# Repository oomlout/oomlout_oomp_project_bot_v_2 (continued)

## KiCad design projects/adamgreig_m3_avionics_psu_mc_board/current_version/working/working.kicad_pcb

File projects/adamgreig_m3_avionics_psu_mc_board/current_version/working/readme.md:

# m3_avionics
 
## summary 
* id: adamgreig_m3_avionics_psu_mc_board
* user: adamgreig
* name: m3_avionics
* board: psu_mc_board
* repo: https://github.com/adamgreig/m3-avionics
* src_file_repo_kicad_pcb: m3psu/pcb/PSU-MC-Board/PSU-MC-Board.kicad_pcb
* src_file_repo_kicad_pcb_link: https://github.com/adamgreig/m3-avionics/tree/master/m3psu/pcb/PSU-MC-Board/PSU-MC-Board.kicad_pcb

* src_file_repo_sch: m3psu/pcb/PSU-MC-Board/PSU-MC-Board.sch
* src_file_repo_sch_link: https://github.com/adamgreig/m3-avionics/tree/master/m3psu/pcb/PSU-MC-Board/PSU-MC-Board.sch
* full details link: https://github.com/oomlout/oomlout_oomp_project_bot_v_2/tree/main/projects/adamgreig_m3_avionics_psu_mc_board/current_version/working  

## schematic  
  
[schematic (pdf)](working_schematic.pdf) 

## pcb  

[board (pdf)](working.pdf)  

## working_bom
| Id | Designator | Footprint | Quantity | Designation | Supplier and ref |  | None | 
| --- | --- | --- | --- | --- | --- | --- | --- | 
| 1 | C1,C2 | 0402 | 2 | 10p |  |  | [''] | 
| 2 | C3 | 0402 | 1 | 4Âµ7 |  |  | [''] | 
| 3 | C4,C5,C7,C8,C9,C16,C19,C20 | 0402 | 8 | 100n |  |  | [''] | 
| 4 | C6 | 0402 | 1 | 1Âµ |  |  | [''] | 
| 5 | C10,C11 | 0402 | 2 | 2Âµ2 |  |  | [''] | 
| 6 | C12,C14 | 0805 | 2 | 22Âµ |  |  | [''] | 
| 7 | C13 | 0402 | 1 | 3n3 |  |  | [''] | 
| 8 | IC1 | LQFP-64 | 1 | STM32F405RxTx |  |  | [''] | 
| 9 | IC2 | QFN-16-EP-TI | 1 | TPS62152 |  |  | [''] | 
| 10 | IC3 | DFN-8-EP-MICROCHIP | 1 | MCP2562 |  |  | [''] | 
| 11 | IC5 | DFN-10-EP-LT | 1 | LTC4151 |  |  | [''] | 
| 12 | J1 | TFML-110-02-L-D | 1 | WEST TOP |  |  | [''] | 
| 13 | J3 | TFML-105-02-L-D | 1 | NORTH TOP |  |  | [''] | 
| 14 | J4 | TFML-110-02-L-D | 1 | EAST TOP |  |  | [''] | 
| 15 | L1 | VLS201610HBX-1 | 1 | 3Âµ3 |  |  | [''] | 
| 16 | Q9,Q2 | SOT-883-B | 2 | NFET |  |  | [''] | 
| 17 | R3 | 0402 | 1 | 100 |  |  | [''] | 
| 18 | R7,R8,R10 | 0402 | 3 | 4k7 |  |  | [''] | 
| 19 | R15 | 0805 | 1 | 10m |  |  | [''] | 
| 20 | R16,R23,R4,R5 | 0402 | 4 | 33k |  |  | [''] | 
| 21 | Y1 | XTAL-20x16 | 1 | 26M |  |  | [''] | 
| 22 | Q8,Q1 | SON2x2 | 2 | PFET |  |  | [''] | 
| 23 | R1,R2 | 0402 | 2 | 100k |  |  | [''] | 
| 24 | J2 | SFML-110-02-L-D-LC | 1 | WEST BOT |  |  | [''] | 
| 25 | J5 | SFML-110-02-L-D-LC | 1 | EAST BOT |  |  | [''] | 
| 26 | G*** | cusf_logo_full | 1 | LOGO |  |  | [''] | 

## bom_schematic
| Ref | Qnty | Value | Cmp name | Footprint | Description | Vendor | DNP | 
| --- | --- | --- | --- | --- | --- | --- | --- | 
| C1, C2 | 2 | 10p | C | agg:0402 |  |  |  | 
| C3 | 1 | 4Âµ7 | C | agg:0402 |  |  |  | 
| C4, C5, C7, C8, C9, C16, C19, C20 | 8 | 100n | C | agg:0402 |  |  |  | 
| C6 | 1 | 1Âµ | C | agg:0402 |  |  |  | 
| C10, C11 | 2 | 2Âµ2 | C | agg:0402 |  |  |  | 
| C12, C14 | 2 | 22Âµ | C | agg:0805 |  |  |  | 
| C13 | 1 | 3n3 | C | agg:0402 |  |  |  | 
| IC1 | 1 | STM32F405RxTx | STM32F405RxTx | agg:LQFP-64 |  |  |  | 
| IC2 | 1 | TPS62152 | TPS62152 | agg:QFN-16-EP-TI |  |  |  | 
| IC3 | 1 | MCP2562 | MCP2562 | agg:DFN-8-EP-MICROCHIP |  |  |  | 
| IC5 | 1 | LTC4151 | LTC4151 | agg:DFN-10-EP-LT |  |  |  | 
| J1 | 1 | WEST TOP | CONN_02x10 | agg:TFML-110-02-L-D |  |  |  | 
| J2 | 1 | WEST BOT | CONN_02x10 | agg:SFML-110-02-L-D-LC |  |  |  | 
| J3 | 1 | NORTH TOP | CONN_02x05 | agg:TFML-105-02-L-D |  |  |  | 
| J4 | 1 | EAST TOP | CONN_02x10 | agg:TFML-110-02-L-D |  |  |  | 
| J5 | 1 | EAST BOT | CONN_02x10 | agg:SFML-110-02-L-D-LC |  |  |  | 
| L1 | 1 | 3Âµ3 | L | agg:VLS201610HBX-1 |  |  |  | 
| Q1, Q8 | 2 | PFET | PFET_GDS | agg:SON2x2 |  |  |  | 
| Q2, Q9 | 2 | NFET | NFET_GDS | agg:SOT-883-B |  |  |  | 
| R1, R2 | 2 | 100k | R | agg:0402 |  |  |  | 
| R3 | 1 | 100 | R | agg:0402 |  |  |  | 
| R4, R5, R16, R23 | 4 | 33k | R | agg:0402 |  |  |  | 
| R7, R8, R10 | 3 | 4k7 | R | agg:0402 |  |  |  | 
| R15 | 1 | 10m | R | agg:0805 |  |  |  | 
| Y1 | 1 | 26M | SMD_XTAL | agg:XTAL-20x16 |  |  |  |

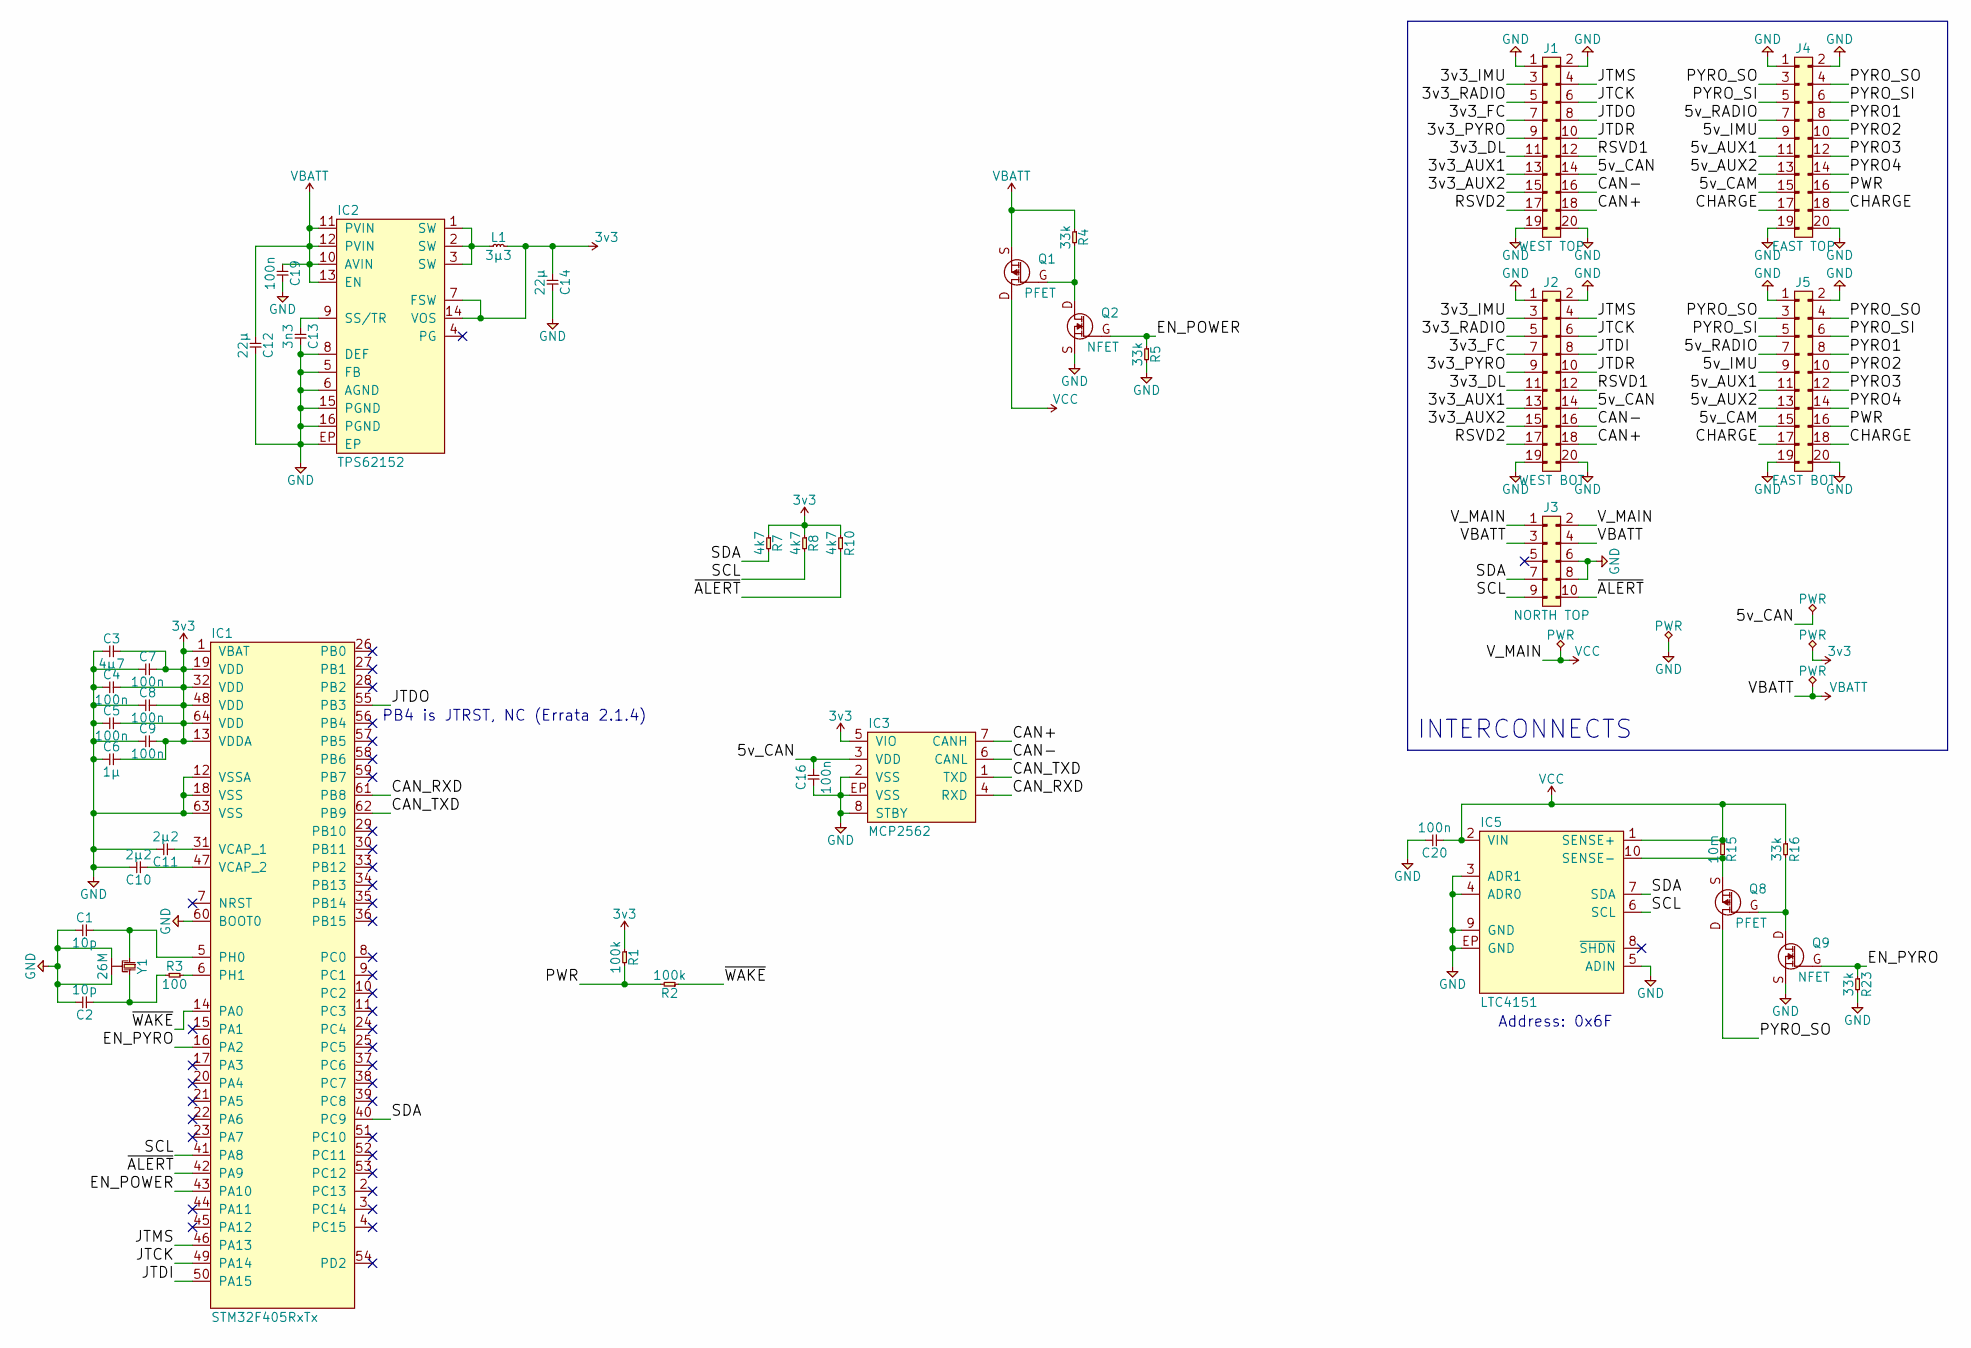
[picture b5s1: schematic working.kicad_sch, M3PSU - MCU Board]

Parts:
C1, C2: 10p; 0402; Farnell 2496790
C3: 4µ7; 0402; Farnell 2426952
C4, C5, C7, C8, C9, C16, C19, C20: 100n; 0402; Farnell 2496771
C6: 1µ; 0402; Farnell 2496814
C10, C11: 2µ2; 0402; Farnell 2362088
C12, C14: 22µ; 0805; Farnell 1907510
C13: 3n3; 0402; Farnell 1758918
IC1: STM32F405RxTx; LQFP-64; Farnell 2064363
IC2: TPS62152; QFN-16-EP-TI; Farnell 2382918
IC3: MCP2562; DFN-8-EP-MICROCHIP; Farnell 2448755
IC5: LTC4151; DFN-10-EP-LT; Farnell 2295457
J1: WEST TOP; TFML-110-02-L-D
J2: WEST BOT; SFML-110-02-L-D-LC
J3: NORTH TOP; TFML-105-02-L-D
J4: EAST TOP; TFML-110-02-L-D
J5: EAST BOT; SFML-110-02-L-D-LC
L1: 3µ3; VLS201610HBX-1; Farnell 2455373
Q1, Q8: PFET; SON2x2; Farnell 2501102
Q2, Q9: NFET; SOT-883-B; Farnell 2498598
R1, R2: 100k; 0402; Farnell 9239472
R3: 100; 0402; Farnell 9239111
R4, R5, R16, R23: 33k; 0402; Farnell 2447160
R7, R8, R10: 4k7; 0402; Farnell 2447187
R15: 10m; 0805; Farnell 2503034
Y1: 26M; XTAL-20x16; Farnell 2506952

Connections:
3v3: C3.2, C4.2, C5.2, C6.2, C7.2, C8.2, C9.2, C14.1, IC1.1 (VBAT), IC1.13 (VDDA), IC1.19 (VDD), IC1.32 (VDD), IC1.48 (VDD), IC1.64 (VDD), IC2.7 (FSW), IC2.14 (VOS), IC3.5 (VIO), L1.2, R1.1, R7.1, R8.1, R10.1
/3v3_AUX1: J1.13, J2.13
/3v3_AUX2: J1.15, J2.15
/3v3_DL: J1.11, J2.11
/3v3_FC: J1.7, J2.7
/3v3_IMU: J1.3, J2.3
/3v3_PYRO: J1.9, J2.9
/3v3_RADIO: J1.5, J2.5
/5v_AUX1: J4.11, J5.11
/5v_AUX2: J4.13, J5.13
/5v_CAM: J4.15, J5.15
/5v_CAN: C16.1, IC3.3 (VDD), J1.14, J2.14
/5v_IMU: J4.9, J5.9
/5v_RADIO: J4.7, J5.7
/CAN+: IC3.7 (CANH), J1.18, J2.18
/CAN-: IC3.6 (CANL), J1.16, J2.16
/CAN_RXD: IC1.61 (PB8), IC3.4 (RXD)
/CAN_TXD: IC1.62 (PB9), IC3.1 (TXD)
/CHARGE: J4.17, J4.18, J5.17, J5.18
/EN_POWER: IC1.43 (PA10), Q2.G, R5.1
/EN_PYRO: IC1.16 (PA2), Q9.G, R23.1
/JTCK: IC1.49 (PA14), J1.6, J2.6
/JTDI: IC1.50 (PA15), J2.8
/JTDO: IC1.55 (PB3), J1.8
/JTDR: J1.10, J2.10
/JTMS: IC1.46 (PA13), J1.4, J2.4
/PWR: J4.16, J5.16, R1.2, R2.2
/PYRO1: J4.8, J5.8
/PYRO2: J4.10, J5.10
/PYRO3: J4.12, J5.12
/PYRO4: J4.14, J5.14
/PYRO_SI: J4.5, J4.6, J5.5, J5.6
/PYRO_SO: J4.3, J4.4, J5.3, J5.4, Q8.D
/RSVD1: J1.12, J2.12
/RSVD2: J1.17, J2.17
/SCL: IC1.41 (PA8), IC5.6 (SCL), J3.9, R8.2
/SDA: IC1.40 (PC9), IC5.7 (SDA), J3.7, R7.2
/~ALERT: IC1.42 (PA9), J3.10, R10.2
/~WAKE: IC1.14 (PA0), R2.1
GND: C1.1, C2.2, C3.1, C4.1, C5.1, C6.1, C7.1, C8.1, C9.1, C10.2, C11.2, C12.2, C13.2, C14.2, C16.2, C19.2, C20.2, IC1.12 (VSSA), IC1.18 (VSS), IC1.60 (BOOT0), IC1.63 (VSS), IC2.5 (FB), IC2.6 (AGND), IC2.8 (DEF), IC2.15 (PGND), IC2.16 (PGND), IC2.EP, IC3.2 (VSS), IC3.8 (STBY), IC3.EP (VSS), IC5.3 (ADR1), IC5.4 (ADR0), IC5.5 (ADIN), IC5.9 (GND), IC5.EP (GND), J1.1, J1.2, J1.19, J1.20, J2.1, J2.2, J2.19, J2.20, J3.6, J3.8, J4.1, J4.2, J4.19, J4.20, J5.1, J5.2, J5.19, J5.20, Q2.S, Q9.S, R5.2, R23.2, Y1.2, Y1.4
unnamed: C1.2, IC1.5 (PH0), Y1.1
unnamed: C2.1, R3.1, Y1.3
unnamed: C10.1, IC1.47 (VCAP_2)
unnamed: C11.1, IC1.31 (VCAP_1)
unnamed: C13.1, IC2.9 (SS/TR)
unnamed: IC1.6 (PH1), R3.2
unnamed: IC2.1 (SW), IC2.2 (SW), IC2.3 (SW), L1.1
unnamed: IC5.10 (SENSE-), Q8.S, R15.2
unnamed: Q1.G, Q2.D, R4.2
unnamed: Q8.G, Q9.D, R16.2
VBATT: C12.1, C19.1, IC2.10 (AVIN), IC2.11 (PVIN), IC2.12 (PVIN), IC2.13 (EN), J3.3, J3.4, Q1.S, R4.1
VCC: C20.1, IC5.1 (SENSE+), IC5.2 (VIN), J3.1, J3.2, Q1.D, R15.1, R16.1

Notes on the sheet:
Address: 0x6F
INTERCONNECTS
PB4 is JTRST, NC (Errata 2.1.4)

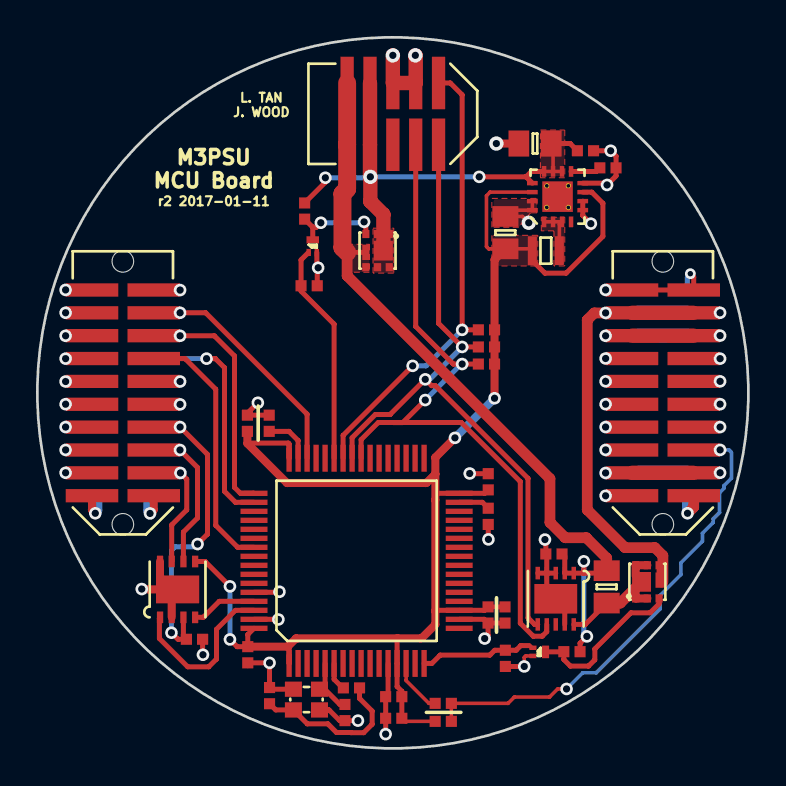
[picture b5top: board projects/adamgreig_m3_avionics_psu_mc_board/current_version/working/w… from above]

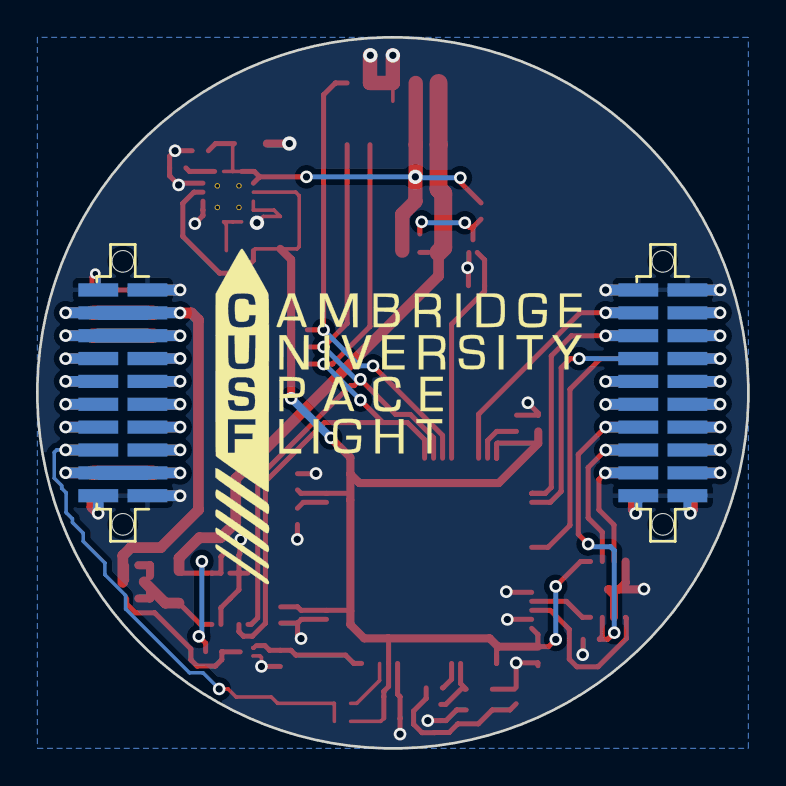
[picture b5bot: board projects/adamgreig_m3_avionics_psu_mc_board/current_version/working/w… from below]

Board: 2 copper layers, 39.5 x 39.5 mm, 43 parts (2 on the bottom side), 52 nets.
